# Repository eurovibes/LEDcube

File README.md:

<!-- SPDX-FileCopyrightText: 2021 Benedikt Spranger <b.spranger@linutronix.de> -->
<!-- SPDX-License-Identifier: CERN-OHL-S-2.0 -->

# LEDcube -  Olimex STMP157-OLinuXino-LIME2 Sensor and Motor shield

## License rules

LEDcube is provided under the terms of the CERN-OHL-S license
version 2 as provided in the LICENSES/CERN-OHL-S-2.0 file.

Instead of adding license boilerplates to the individual files,
LEDcube uses SPDX license identifiers, which are machine parseable
and considered legaly equivalent.

The SPDX license identifier in LEDcube shall be added at the first
possible line in a file which can contain a comment. This is normally the
first line except for scripts. Scripts require the #!PATH_TO_INTERPRETER tag
in the first line; place the SPDX identifier into the second line.

The SPDX license identifier is added in form of a comment.

## Copyright and License

> Copyright Benedikt Spranger 2021.
> This source describes Open Hardware and is licensed under the CERNOHL-S v2.
> You may redistribute and modify this source and make products using it
> under the terms of the CERN-OHL-S v2 (https://ohwr.org/cern ohl s v2.txt ).
> This source is distributed WITHOUT ANY EXPRESS OR IMPLIED WARRANTY, INCLUDING
> OF MERCHANTABILITY, SATISFACTORY QUALITY AND FITNESS FOR A PARTICULAR PURPOSE.
> Please see the CERN-OHL-S v2 for applicable conditions.
> Source location: https://github.com/eurovibes/LEDcube
> As per CERN-OHL-S v2 section 4, should You produce hardware based
> on this source, You must where practicable maintain the Source Location
> visible on the external case of the LEDcube or other products you
> make using this source.

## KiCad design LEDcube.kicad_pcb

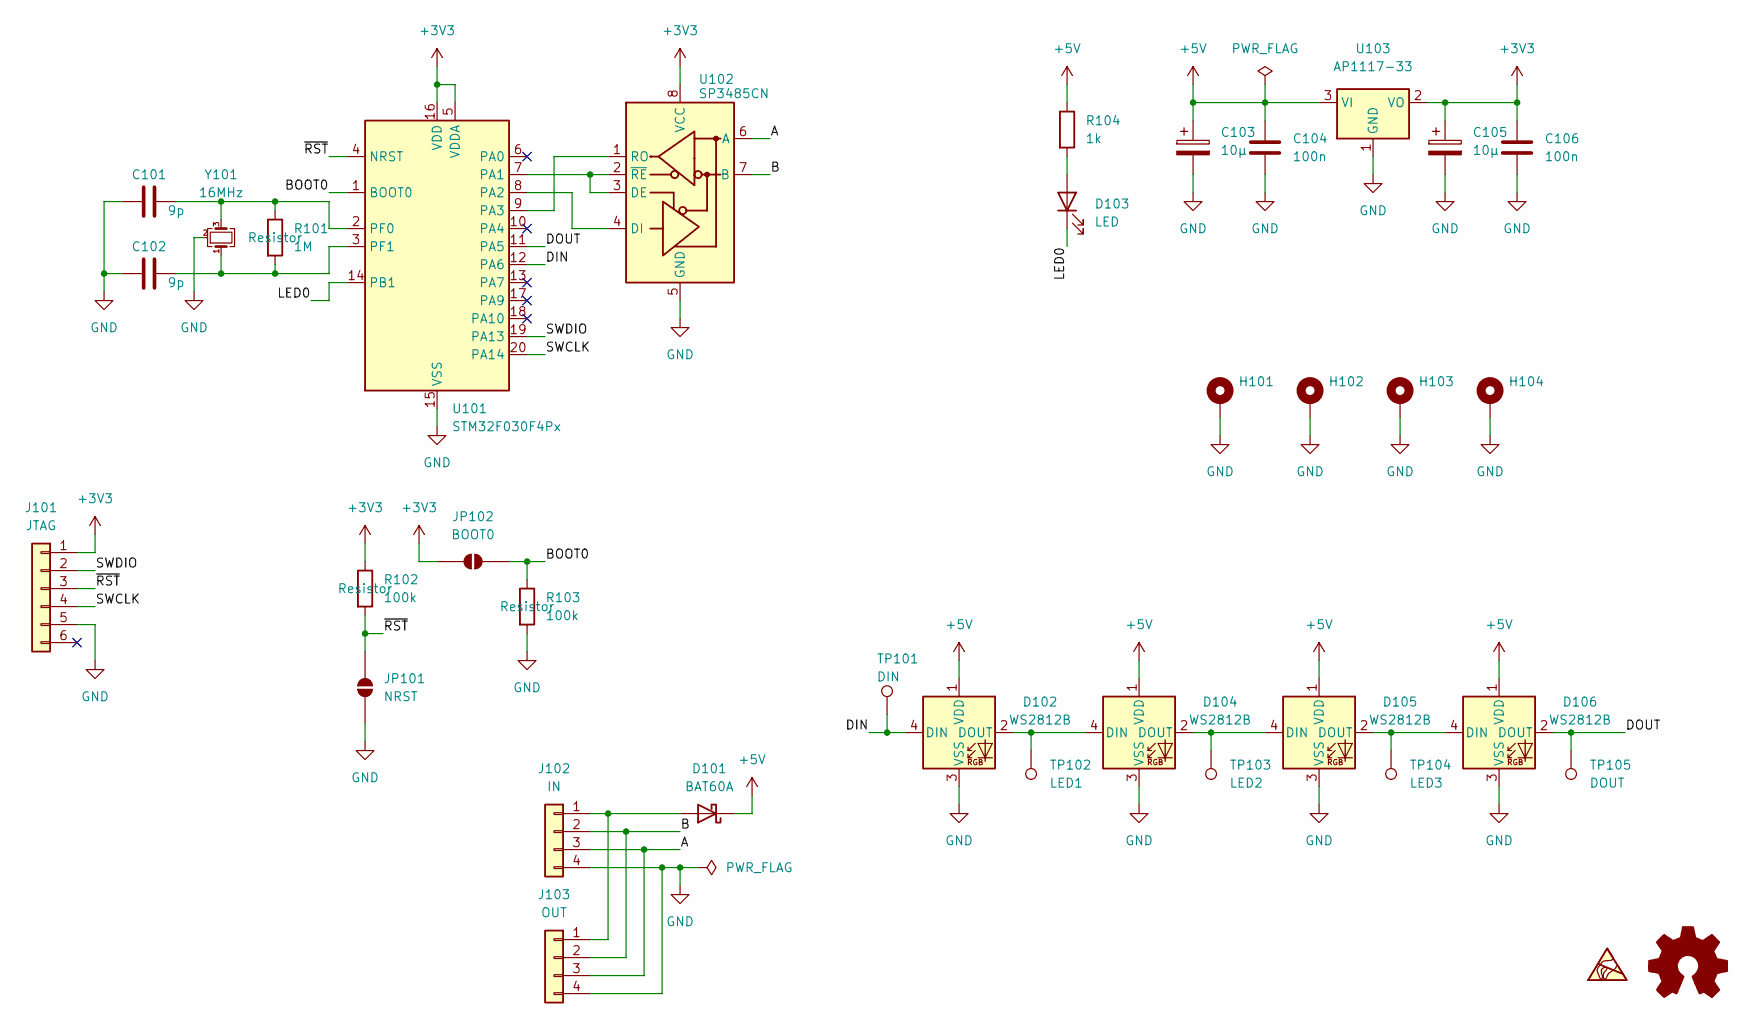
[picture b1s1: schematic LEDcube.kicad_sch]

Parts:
C101, C102: 9p; C_0402_1005Metric; ManuPart# CL05C100JB5NNNC; LCSC# C32949
C103, C105: 10µ; CP_EIA-3216-18_Kemet-A; ManuPart# TAJA106K016RNJ; LCSC# C7171
C104, C106: 100n; C_0402_1005Metric; ManuPart# CL05B104KO5NNNC; LCSC# C1525
D101: BAT60A; D_SOD-323; ManuPart# BAT60AE6327H; LCSC# C520634
D102, D104, D105, D106: WS2812B; LED_WS2812B_PLCC4_5.0x5.0mm_P3.2mm; ManuPart# WS2812B-B/W; LCSC# C2761795
D103: LED; LED_0603_1608Metric; ManuPart# KT-0603R; LCSC# C2286
H101, H102, H103, H104: MountingHole_3.2mm_M3_ISO14580_Pad; ManuPart# ---
J101: JTAG; Tag-Connect_TC2030-IDC-FP_2x03_P1.27mm_Vertical
J102: IN; PinHeader_1x04_P2.54mm_Vertical; ManuPart# DS1021-1*4SF11-B
J103: OUT; PinHeader_1x04_P2.54mm_Vertical; ManuPart# DS1021-1*4SF11-B
JP101: NRST; SolderJumper-2_P1.3mm_Open_RoundedPad1.0x1.5mm; ManuPart# ---
JP102: BOOT0; SolderJumper-2_P1.3mm_Open_RoundedPad1.0x1.5mm; ManuPart# ---
R101: 1M; R_0402_1005Metric; ManuPart# 0402WGF1004TCE; LCSC# C26083
R102, R103: 100k; R_0402_1005Metric; ManuPart# 0402WGF1003TCE; LCSC# C25741
R104: 1k; R_0402_1005Metric; ManuPart# 0402WGF1001TCE; LCSC# C11702
TP101: DIN; TestPoint_Pad_D1.0mm; ManuPart# ---
TP102: LED1; TestPoint_Pad_D1.0mm; ManuPart# ---
TP103: LED2; TestPoint_Pad_D1.0mm; ManuPart# ---
TP104: LED3; TestPoint_Pad_D1.0mm; ManuPart# ---
TP105: DOUT; TestPoint_Pad_D1.0mm; ManuPart# ---
U101: STM32F030F4Px; TSSOP-20_4.4x6.5mm_P0.65mm; ManuPart# STM32F030F4P6TR; LCSC# C89040
U102: SP3485CN; SOIC-8_3.9x4.9mm_P1.27mm; ManuPart# SP3485EN-L/TR; LCSC# C8963
U103: AP1117-33; SOT-223-3_TabPin2; ManuPart# AP1117E33G-13; LCSC# C108785
Y101: 16MHz; Crystal_SMD_3225-4Pin_3.2x2.5mm; ManuPart# X322516MLB4SI; LCSC# C13738

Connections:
+3V3: C105.1, C106.2, J101.1, JP102.1 (A), R102.1, U101.5 (VDDA), U101.16 (VDD), U102.8 (VCC), U103.2 (VO)
+5V: C103.1, C104.2, D101.1 (K), D102.1 (VDD), D104.1 (VDD), D105.1 (VDD), D106.1 (VDD), R104.1, U103.3 (VI)
/A: J102.3, J103.3, U102.6 (A)
/B: J102.2, J103.2, U102.7 (B)
/BOOT0: JP102.2 (B), R103.1, U101.1 (BOOT0)
/DIN: D102.4 (DIN), TP101.1 (1_1), U101.12 (PA6)
/DOUT: D106.2 (DOUT), TP105.1 (1_1), U101.11 (PA5)
/LED0: D103.1 (K), U101.14 (PB1)
/SWCLK: J101.4, U101.20 (PA14)
/SWDIO: J101.2, U101.19 (PA13)
/~RST: J101.3, JP101.1 (A), R102.2, U101.4 (NRST)
GND: C101.1, C102.1, C103.2, C104.1, C105.2, C106.1, D102.3 (VSS), D104.3 (VSS), D105.3 (VSS), D106.3 (VSS), H101.1 (1_1), H102.1 (1_1), H103.1 (1_1), H104.1 (1_1), J101.5, J102.4, J103.4, JP101.2 (B), R103.2, U101.15 (VSS), U102.5 (GND), U103.1 (GND), Y101.2 (G), Y101.4 (G)
unnamed: D101.2 (A), J102.1, J103.1
unnamed: D102.2 (DOUT), D104.4 (DIN), TP102.1 (1_1)
unnamed: D103.2 (A), R104.2
unnamed: D104.2 (DOUT), D105.4 (DIN), TP103.1 (1_1)
unnamed: D105.2 (DOUT), D106.4 (DIN), TP104.1 (1_1)
unnamed: U101.7 (PA1), U102.2 (~RE), U102.3 (DE)
unnamed: U101.8 (PA2), U102.4 (DI)
unnamed: U101.9 (PA3), U102.1 (RO)
unnamed: C101.2, R101.1, U101.2 (PF0), Y101.3
unnamed: C102.2, R101.2, U101.3 (PF1), Y101.1

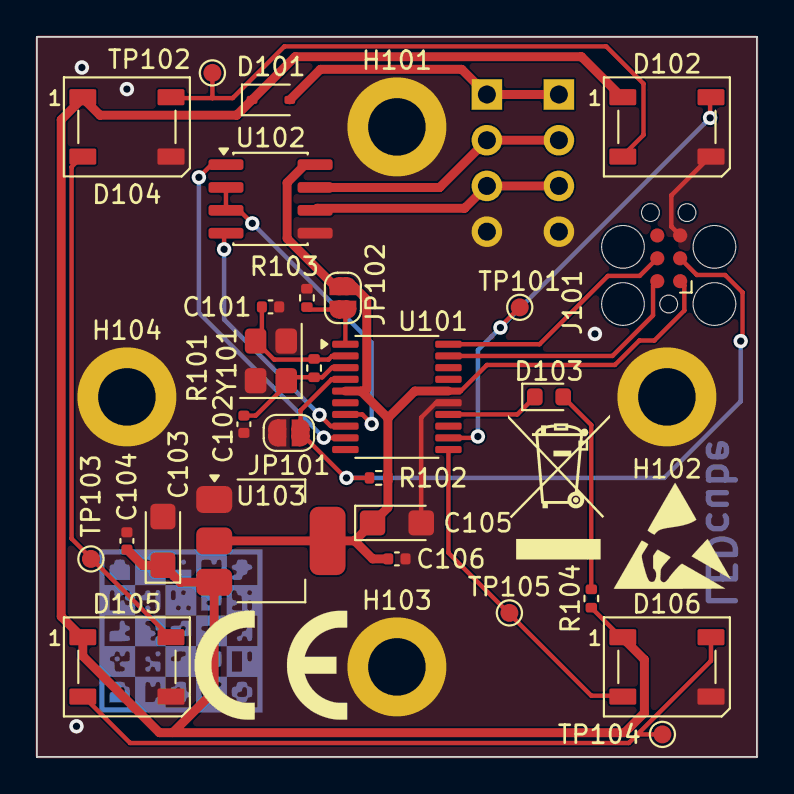
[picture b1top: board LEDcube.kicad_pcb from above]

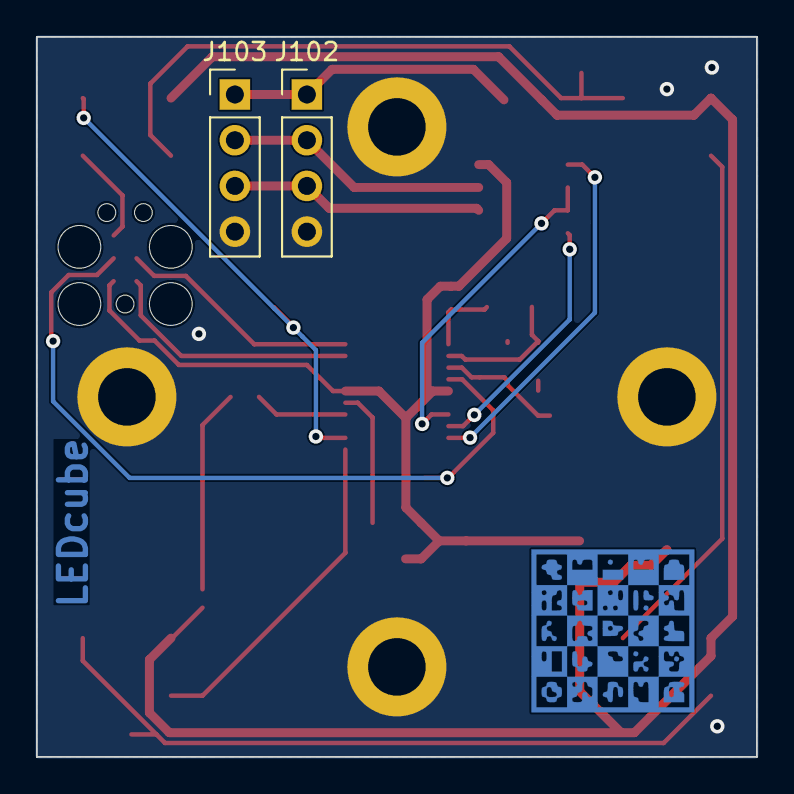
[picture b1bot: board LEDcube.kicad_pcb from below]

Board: 2 copper layers, 40.0 x 40.0 mm, 38 parts (3 on the bottom side), 22 nets.

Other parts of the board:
SYM1: LOGO
SYM2: WEEE-Logo_5.6x8mm_SilkScreen
SYM3: ESD-Logo_6.6x6mm_SilkScreen
SYM4: CE-Logo_8.5x6mm_SilkScreen

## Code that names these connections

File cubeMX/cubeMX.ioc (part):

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Mcu.Name=STM32F030F4Px
Mcu.Package=TSSOP20
Mcu.UserName=STM32F030F4Px
PA1.Mode=Hardware Flow Control (RS485)
PA1.Signal=USART1_DE
PA13.Mode=Serial_Wire
PA13.Signal=SYS_SWDIO
PA14.Mode=Serial_Wire
PA14.Signal=SYS_SWCLK
PA2.Mode=Asynchronous
PA2.Signal=USART1_TX
PA3.Mode=Asynchronous
PA3.Signal=USART1_RX
PA4.GPIOParameters=GPIO_Label
PA4.GPIO_Label=DIN
PA4.Signal=GPIO_Input
PA6.Signal=S_TIM3_CH1
PF0-OSC_IN.Mode=HSE-External-Oscillator
PF0-OSC_IN.Signal=RCC_OSC_IN
PF1-OSC_OUT.Mode=HSE-External-Oscillator
PF1-OSC_OUT.Signal=RCC_OSC_OUT
RCC.HSE_VALUE=16000000
RCC.SYSCLKFreq_VALUE=48000000
RCC.SYSCLKSource=RCC_SYSCLKSOURCE_PLLCLK
board=custom

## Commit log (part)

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2022-05-22 Initial
2022-05-23 Add software
2022-05-23 Initial gh-pages commit
2022-05-23 Deploying to gh-pages from @ eurovibes/LEDcube@76d650e751ab3897b6da312312fd24e9727ce052 🚀
2022-05-25 enclosure: Add cube connection element
2022-08-22 Crystal related fixes
2022-08-22 enclosure rework to fit JLCPCB requirements
2022-08-22 Always run actions on push to master
2022-08-22 Do not ignore changes to github actions
2022-08-22 Use KiBot v1
2022-08-22 Deploying to gh-pages from @ eurovibes/LEDcube@a7234f0d9a771873ee846fc7fcf68f8b4e66b4fe 🚀

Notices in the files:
LEDcube.kicad_sch:
This work is licensed under the CERN-OHL-S v2
